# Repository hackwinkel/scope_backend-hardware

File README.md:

# 100Ms/s dual channel 16 bitdigital oscilloscope and function generator back-end with ethernet 

This repository contains the schematics and PCB design files.

# Main features
- 100MHz sample rate
- 2 channels, 16 bits A/D
- 4 channels, 14 bits D/A
- 256 Mbyte ddr3 ram
- Gigabit Ethernet

# General description
Please refer to the hierarchical schematic diagram provided in this repository

* Main (contains various digital power supplies and references to subsheets)
   * FPGA (contains the FPGA with its power connections, JTAG and signal definitions)
   * DACS (contains the D / A convertors with analogue power supplies and output buffers)
   * ADCS (contains the A/D convertors with analogue power supplies and input buffers)
   * ddr3 (contains memory with terminations)
   * GNET (contains Gbit ethernet PHY with magnetics and support components)

## Power supplies
All power supplies are standard LDO regulators, stepping down the voltages from a main 5V connection. To limit dissipation in each LDO, multiple 3.3V, 2.5V, 1.5V and 1.2V subnets are used, and the lower voltages are stepped down via an intermediary 3.3V stage.
The only exception is an optional switched mode power supply module providing +9V/-9V for analogue input/output buffers. This module is optional if the analogue front-end is used, as this also provides these voltages.

## FPGA
This project uses a SPARTAN 6 Field Programmable Logic Array (XC6SLX16 FPLA) at its heart. This FPLA device digitally connects all components, and allows this project to be flexibly reconfigured for various purposes. Core timing is provided by a 100MHz integrated crystal oscillator and a 125MHz clock derived from the ethernet PHY 

## DACS
Digital-to-Analogue conversion is performed by 4 DAC904 165 Msample/s 14 bit D/A convertors. Each of these D/A convertors has its own 3.3V power supply. The DAC904 produces a differential output signal, which is converted and buffered to a single ended signal using an OPA695 operational amplifier.

## ADCS
Analogue-to-Digital conversion is performed by 2 LTC2208 130 Msample/s 16 bit A/D convertors. Each of these A/D convertors has its own 3.3V power supply. For each A/D convertor an AD8138 diferential amplifier provides the required buffered differential analogue drive signal. These AD8138 are by default configured to convert a single ended signal to a differential signal.

## ddr3
A single MT41K128M16 ddr3 RAM chip provides 128M x 16 memory. This has to be a 1.5V compatible device as the SPARTAN 6 FPGA does not support 1.35V memory. Single ended, single direction lines (address and some control signals) are unterminated as this apparently "just works"-albeit probably not at maximum speed. Bidirectional signals are dynamically terminated on the chip. Simple resistive termination is provided on some differential clocking signals. A reference voltage is generated using a resistive divider. All traces on the PCB are length-matched to within 0.5mm

## GNET
A KSZ9031 Gigabit ethernet PHY with Reduced Gigabit Media Independent Interface (RGMII) provides a gigabit ethernet connection through a gigabit MagJack. The local 25Mhz crystal oscillator is converted to a 125MHz clock signal, which is also connected to the FPGA as an alternate timing source

## This project is currently under construction
Most notably, VHDL/Verilog code to program the FPGA is required and an analogue front-end.

# IMPORTANT NOTE FOR PCB FABRICATION

Various PCB houses have various design constraints. JLCPCB has some awkward design rules, requiring a larger space between via-pads and adjacent traces of different nets than between two traces of different nets. KiCAD only allows you to specify *one* spacing for both. In order to accomodate this, the PCB has been designed using 0.508mm vias with 0.2mm holes. Prior to exporting to gerbers, these via pads need to be made smaller in order to compy with these design rules:

Pcbnew -> Setup -> Design rules, change "Via Dia" to 0.45mm
Pcbnew -> Edit -> Edit All Tracks and Vias -> Set all vias (no tracks) to their Netclass value, and OK

## EXPORT GERBERS, DO NOT SAVE THE CHANGED PCB DESIGN FILES as next time you change anything the smaller vias will lead to planes and traces coming too close to the via.

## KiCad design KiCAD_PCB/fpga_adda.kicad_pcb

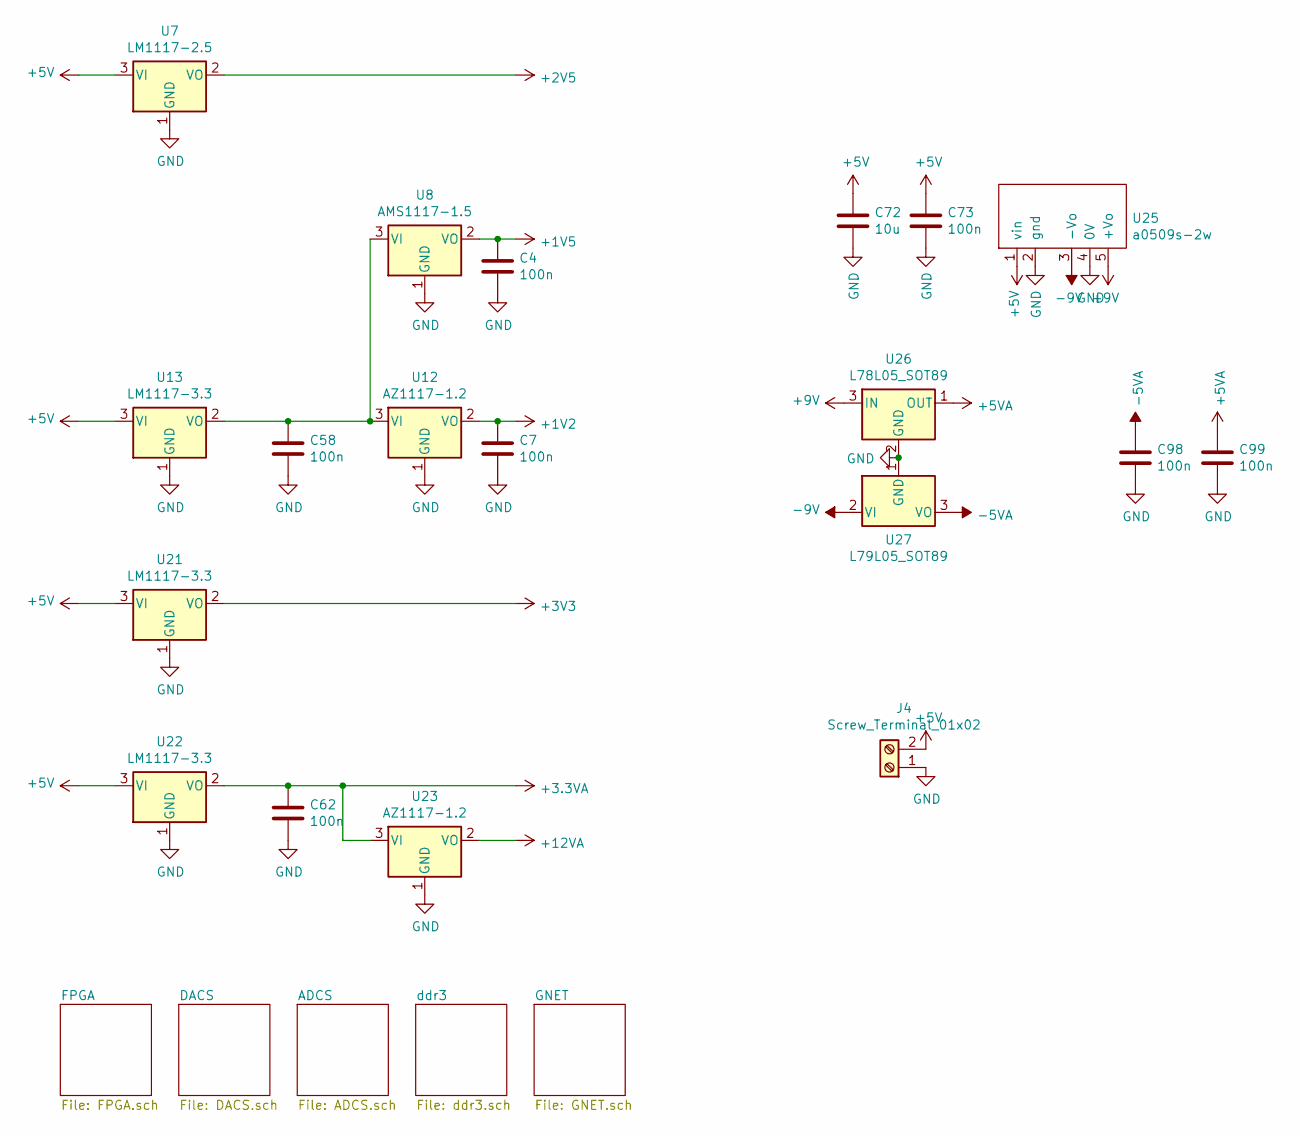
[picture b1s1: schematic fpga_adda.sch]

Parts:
C4, C7, C58, C62, C73, C98, C99: 100n; C_0805_2012Metric_Pad1.15x1.40mm_HandSolder
C72: 10u; C_0805_2012Metric_Pad1.15x1.40mm_HandSolder
J4: Screw_Terminal_01x02; TerminalBlock_bornier-2_P5.08mm
U7: LM1117-2.5; SOT-223-3_TabPin2
U8: AMS1117-1.5; SOT-223-3_TabPin2
U12, U23: AZ1117-1.2; SOT-223-3_TabPin2
U13, U21, U22: LM1117-3.3; SOT-223-3_TabPin2
U25: a0509s-2w
U26: L78L05_SOT89; SOT-89-3
U27: L79L05_SOT89; SOT-89-3

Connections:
+1V2: C7.1, U12.2 (VO); also elsewhere on the board
+1V5: C4.1, U8.2 (VO); also elsewhere on the board
+2V5: U7.2 (VO); also elsewhere on the board
+3.3VA: C62.1, U22.2 (VO), U23.3 (VI); also elsewhere on the board
+5V: C72.1, C73.1, J4.2, U7.3 (VI), U13.3 (VI), U21.3 (VI), U22.3 (VI), U25.1 (vin); also elsewhere on the board
+5VA: C99.1, U26.1 (OUT); also elsewhere on the board
+9V: U25.5 (+Vo), U26.3 (IN)
+12VA: U23.2 (VO); also elsewhere on the board
-5VA: C98.1, U27.3 (VO); also elsewhere on the board
-9V: U25.3 (-Vo), U27.2 (VI)
GND: C4.2, C7.2, C58.2, C62.2, C72.2, C73.2, C98.2, C99.2, J4.1, U7.1 (GND), U8.1 (GND), U12.1 (GND), U13.1 (GND), U21.1 (GND), U22.1 (GND), U23.1 (GND), U25.2 (gnd), U25.4 (0V), U26.2 (GND), U27.1 (GND); also elsewhere on the board
unnamed: C58.1, U8.3 (VI), U12.3 (VI), U13.2 (VO)

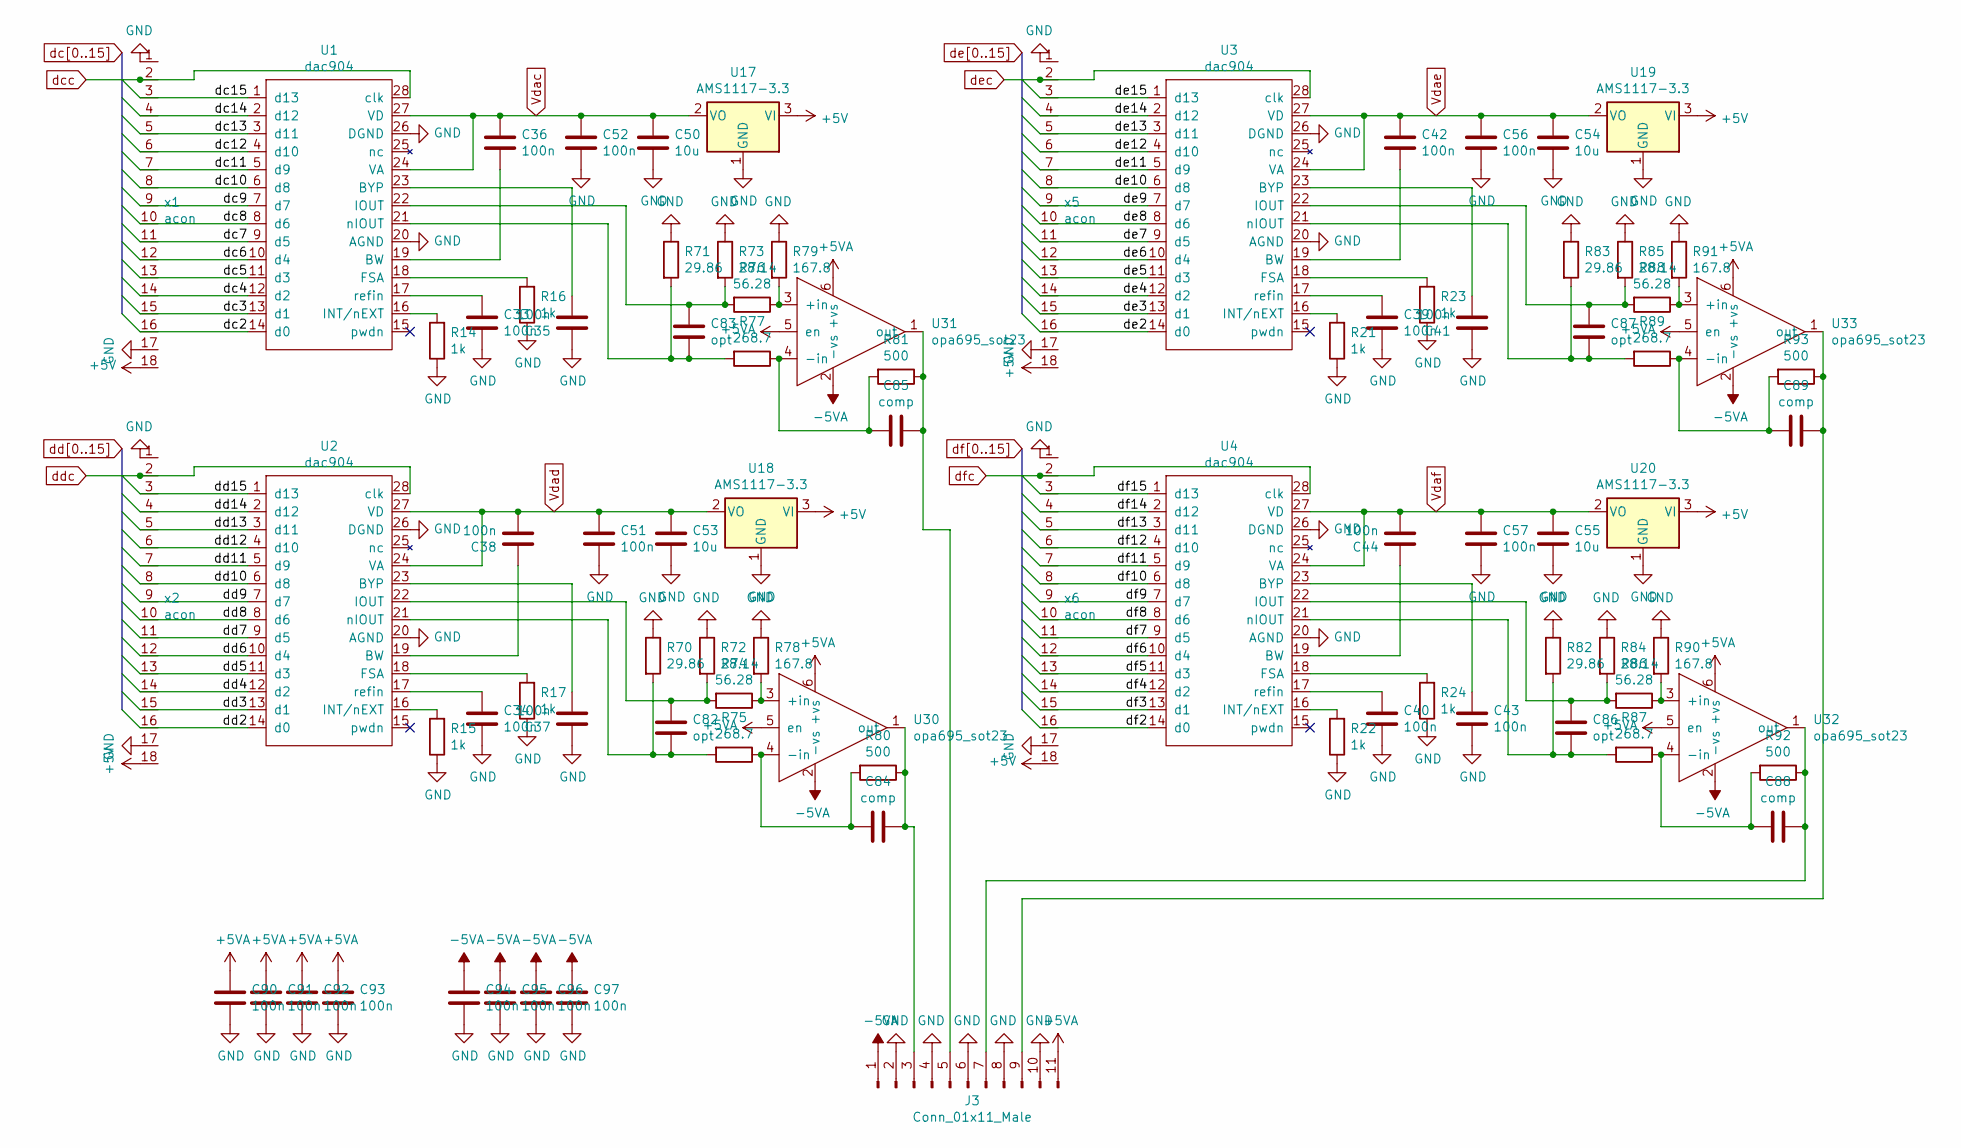
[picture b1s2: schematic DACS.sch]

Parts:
C33, C34, C35, C36, C37, C38, C39, C40, C41, C42, C43, C44, C51, C52, C56, C57, C90, C91, C92, C93, C94, C95, C96, C97: 100n; C_0805_2012Metric_Pad1.15x1.40mm_HandSolder
C50, C53, C54, C55: 10u; C_0805_2012Metric_Pad1.15x1.40mm_HandSolder
C82, C83, C86, C87: opt; C_0805_2012Metric_Pad1.15x1.40mm_HandSolder
C84, C85, C88, C89: comp; C_0805_2012Metric_Pad1.15x1.40mm_HandSolder
J3: Conn_01x11_Male; PinHeader_1x11_P2.54mm_Vertical
R14, R15, R16, R17, R21, R22, R23, R24: 1k; R_0805_2012Metric_Pad1.15x1.40mm_HandSolder
R70, R71, R82, R83: 29.86; R_0805_2012Metric_Pad1.15x1.40mm_HandSolder
R72, R73, R84, R85: 28.14; R_0805_2012Metric_Pad1.15x1.40mm_HandSolder
R74, R76, R86, R88: 56.28; R_0805_2012Metric_Pad1.15x1.40mm_HandSolder
R75, R77, R87, R89: 268.7; R_0805_2012Metric_Pad1.15x1.40mm_HandSolder
R78, R79, R90, R91: 167.8; R_0805_2012Metric_Pad1.15x1.40mm_HandSolder
R80, R81, R92, R93: 500; R_0805_2012Metric_Pad1.15x1.40mm_HandSolder
U1, U2, U3, U4: dac904; SSOP-28_5.3x10.2mm_P0.65mm
U17, U18, U19, U20: AMS1117-3.3; SOT-223-3_TabPin2
U30, U31, U32, U33: opa695_sot23; SOT-23-6_Handsoldering
x1, x2, x5, x6: acon

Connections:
+5V: U17.3 (VI), U18.3 (VI), U19.3 (VI), U20.3 (VI), x1.18, x2.18, x5.18, x6.18; also elsewhere on the board
+5VA: C90.1, C91.1, C92.1, C93.1, J3.11, U30.5 (en), U30.6 (+vs), U31.5 (en), U31.6 (+vs), U32.5 (en), U32.6 (+vs), U33.5 (en), U33.6 (+vs); also elsewhere on the board
-5VA: C94.1, C95.1, C96.1, C97.1, J3.1, U30.2 (-vs), U31.2 (-vs), U32.2 (-vs), U33.2 (-vs); also elsewhere on the board
GND: C33.2, C34.2, C35.1, C37.1, C39.2, C40.2, C41.1, C43.2, C50.2, C51.2, C52.2, C53.2, C54.2, C55.2, C56.2, C57.2, C90.2, C91.2, C92.2, C93.2, C94.2, C95.2, C96.2, C97.2, J3.2, J3.4, J3.6, J3.8, J3.10, R14.1, R15.1, R16.1, R17.1, R21.1, R22.1, R23.1, R24.1, R70.1, R71.1, R72.1, R73.1, R78.1, R79.1, R82.1, R83.1, R84.1, R85.1, R90.1, R91.1, U1.20 (AGND), U1.26 (DGND), U2.20 (AGND), U2.26 (DGND), U3.20 (AGND), U3.26 (DGND), U4.20 (AGND), U4.26 (DGND), U17.1 (GND), U18.1 (GND), U19.1 (GND), U20.1 (GND), x1.1, x1.17, x2.1, x2.17, x5.1, x5.17, x6.1, x6.17; also elsewhere on the board
unnamed: C33.1, U1.17 (refin)
unnamed: C34.1, U2.17 (refin)
unnamed: C35.2, U1.23 (BYP)
unnamed: C36.2, U1.19 (BW)
unnamed: C37.2, U2.23 (BYP)
unnamed: C38.1, U2.19 (BW)
unnamed: C39.1, U3.17 (refin)
unnamed: C40.1, U4.17 (refin)
unnamed: C41.2, U3.23 (BYP)
unnamed: C42.2, U3.19 (BW)
unnamed: C43.1, U4.23 (BYP)
unnamed: C44.1, U4.19 (BW)
unnamed: C82.1, R72.2, R74.2, U2.22 (IOUT)
unnamed: C82.2, R70.2, R75.2, U2.21 (nIOUT)
unnamed: C83.1, R73.2, R76.2, U1.22 (IOUT)
unnamed: C83.2, R71.2, R77.2, U1.21 (nIOUT)
unnamed: C84.1, J3.3, R80.1, U30.1 (out)
unnamed: C84.2, R75.1, R80.2, U30.4 (-in)
unnamed: C85.1, J3.5, R81.1, U31.1 (out)
unnamed: C85.2, R77.1, R81.2, U31.4 (-in)
unnamed: C86.1, R84.2, R86.2, U4.22 (IOUT)
unnamed: C86.2, R82.2, R87.2, U4.21 (nIOUT)
unnamed: C87.1, R85.2, R88.2, U3.22 (IOUT)
unnamed: C87.2, R83.2, R89.2, U3.21 (nIOUT)
unnamed: C88.1, J3.7, R92.1, U32.1 (out)
unnamed: C88.2, R87.1, R92.2, U32.4 (-in)
unnamed: C89.1, J3.9, R93.1, U33.1 (out)
unnamed: C89.2, R89.1, R93.2, U33.4 (-in)
unnamed: R14.2, U1.16 (INT/nEXT)
unnamed: R15.2, U2.16 (INT/nEXT)
unnamed: R16.2, U1.18 (FSA)
unnamed: R17.2, U2.18 (FSA)
unnamed: R21.2, U3.16 (INT/nEXT)
unnamed: R22.2, U4.16 (INT/nEXT)
unnamed: R23.2, U3.18 (FSA)
unnamed: R24.2, U4.18 (FSA)
unnamed: R74.1, R78.2, U30.3 (+in)
unnamed: R76.1, R79.2, U31.3 (+in)
unnamed: R86.1, R90.2, U32.3 (+in)
unnamed: R88.1, R91.2, U33.3 (+in)
Vdac: C36.1, C50.1, C52.1, U1.24 (VA), U1.27 (VD), U17.2 (VO)
Vdad: C38.2, C51.1, C53.1, U2.24 (VA), U2.27 (VD), U18.2 (VO)
Vdae: C42.1, C54.1, C56.1, U3.24 (VA), U3.27 (VD), U19.2 (VO)
Vdaf: C44.2, C55.1, C57.1, U4.24 (VA), U4.27 (VD), U20.2 (VO)
dc2: U1.14 (d0), x1.16; also elsewhere on the board
dc3: U1.13 (d1), x1.15; also elsewhere on the board
dc4: U1.12 (d2), x1.14; also elsewhere on the board
dc5: U1.11 (d3), x1.13; also elsewhere on the board
dc6: U1.10 (d4), x1.12; also elsewhere on the board
dc7: U1.9 (d5), x1.11; also elsewhere on the board
dc8: U1.8 (d6), x1.10; also elsewhere on the board
dc9: U1.7 (d7), x1.9; also elsewhere on the board
dc10: U1.6 (d8), x1.8; also elsewhere on the board
dc11: U1.5 (d9), x1.7; also elsewhere on the board
dc12: U1.4 (d10), x1.6; also elsewhere on the board
dc13: U1.3 (d11), x1.5; also elsewhere on the board
dc14: U1.2 (d12), x1.4; also elsewhere on the board
dc15: U1.1 (d13), x1.3; also elsewhere on the board
dcc: U1.28 (clk), x1.2; also elsewhere on the board
dd2: U2.14 (d0), x2.16; also elsewhere on the board
dd3: U2.13 (d1), x2.15; also elsewhere on the board
dd4: U2.12 (d2), x2.14; also elsewhere on the board
dd5: U2.11 (d3), x2.13; also elsewhere on the board
dd6: U2.10 (d4), x2.12; also elsewhere on the board
dd7: U2.9 (d5), x2.11; also elsewhere on the board
dd8: U2.8 (d6), x2.10; also elsewhere on the board
dd9: U2.7 (d7), x2.9; also elsewhere on the board
dd10: U2.6 (d8), x2.8; also elsewhere on the board
dd11: U2.5 (d9), x2.7; also elsewhere on the board
dd12: U2.4 (d10), x2.6; also elsewhere on the board
dd13: U2.3 (d11), x2.5; also elsewhere on the board
dd14: U2.2 (d12), x2.4; also elsewhere on the board
dd15: U2.1 (d13), x2.3; also elsewhere on the board
ddc: U2.28 (clk), x2.2; also elsewhere on the board
de2: U3.14 (d0), x5.16; also elsewhere on the board
de3: U3.13 (d1), x5.15; also elsewhere on the board
de4: U3.12 (d2), x5.14; also elsewhere on the board
de5: U3.11 (d3), x5.13; also elsewhere on the board
de6: U3.10 (d4), x5.12; also elsewhere on the board
de7: U3.9 (d5), x5.11; also elsewhere on the board
de8: U3.8 (d6), x5.10; also elsewhere on the board
de9: U3.7 (d7), x5.9; also elsewhere on the board
de10: U3.6 (d8), x5.8; also elsewhere on the board
de11: U3.5 (d9), x5.7; also elsewhere on the board
de12: U3.4 (d10), x5.6; also elsewhere on the board
de13: U3.3 (d11), x5.5; also elsewhere on the board
de14: U3.2 (d12), x5.4; also elsewhere on the board
de15: U3.1 (d13), x5.3; also elsewhere on the board
dec: U3.28 (clk), x5.2; also elsewhere on the board
df2: U4.14 (d0), x6.16; also elsewhere on the board
df3: U4.13 (d1), x6.15; also elsewhere on the board
df4: U4.12 (d2), x6.14; also elsewhere on the board
df5: U4.11 (d3), x6.13; also elsewhere on the board
df6: U4.10 (d4), x6.12; also elsewhere on the board
df7: U4.9 (d5), x6.11; also elsewhere on the board
df8: U4.8 (d6), x6.10; also elsewhere on the board
df9: U4.7 (d7), x6.9; also elsewhere on the board
df10: U4.6 (d8), x6.8; also elsewhere on the board
df11: U4.5 (d9), x6.7; also elsewhere on the board
df12: U4.4 (d10), x6.6; also elsewhere on the board
df13: U4.3 (d11), x6.5; also elsewhere on the board
df14: U4.2 (d12), x6.4; also elsewhere on the board
df15: U4.1 (d13), x6.3; also elsewhere on the board
dfc: U4.28 (clk), x6.2; also elsewhere on the board

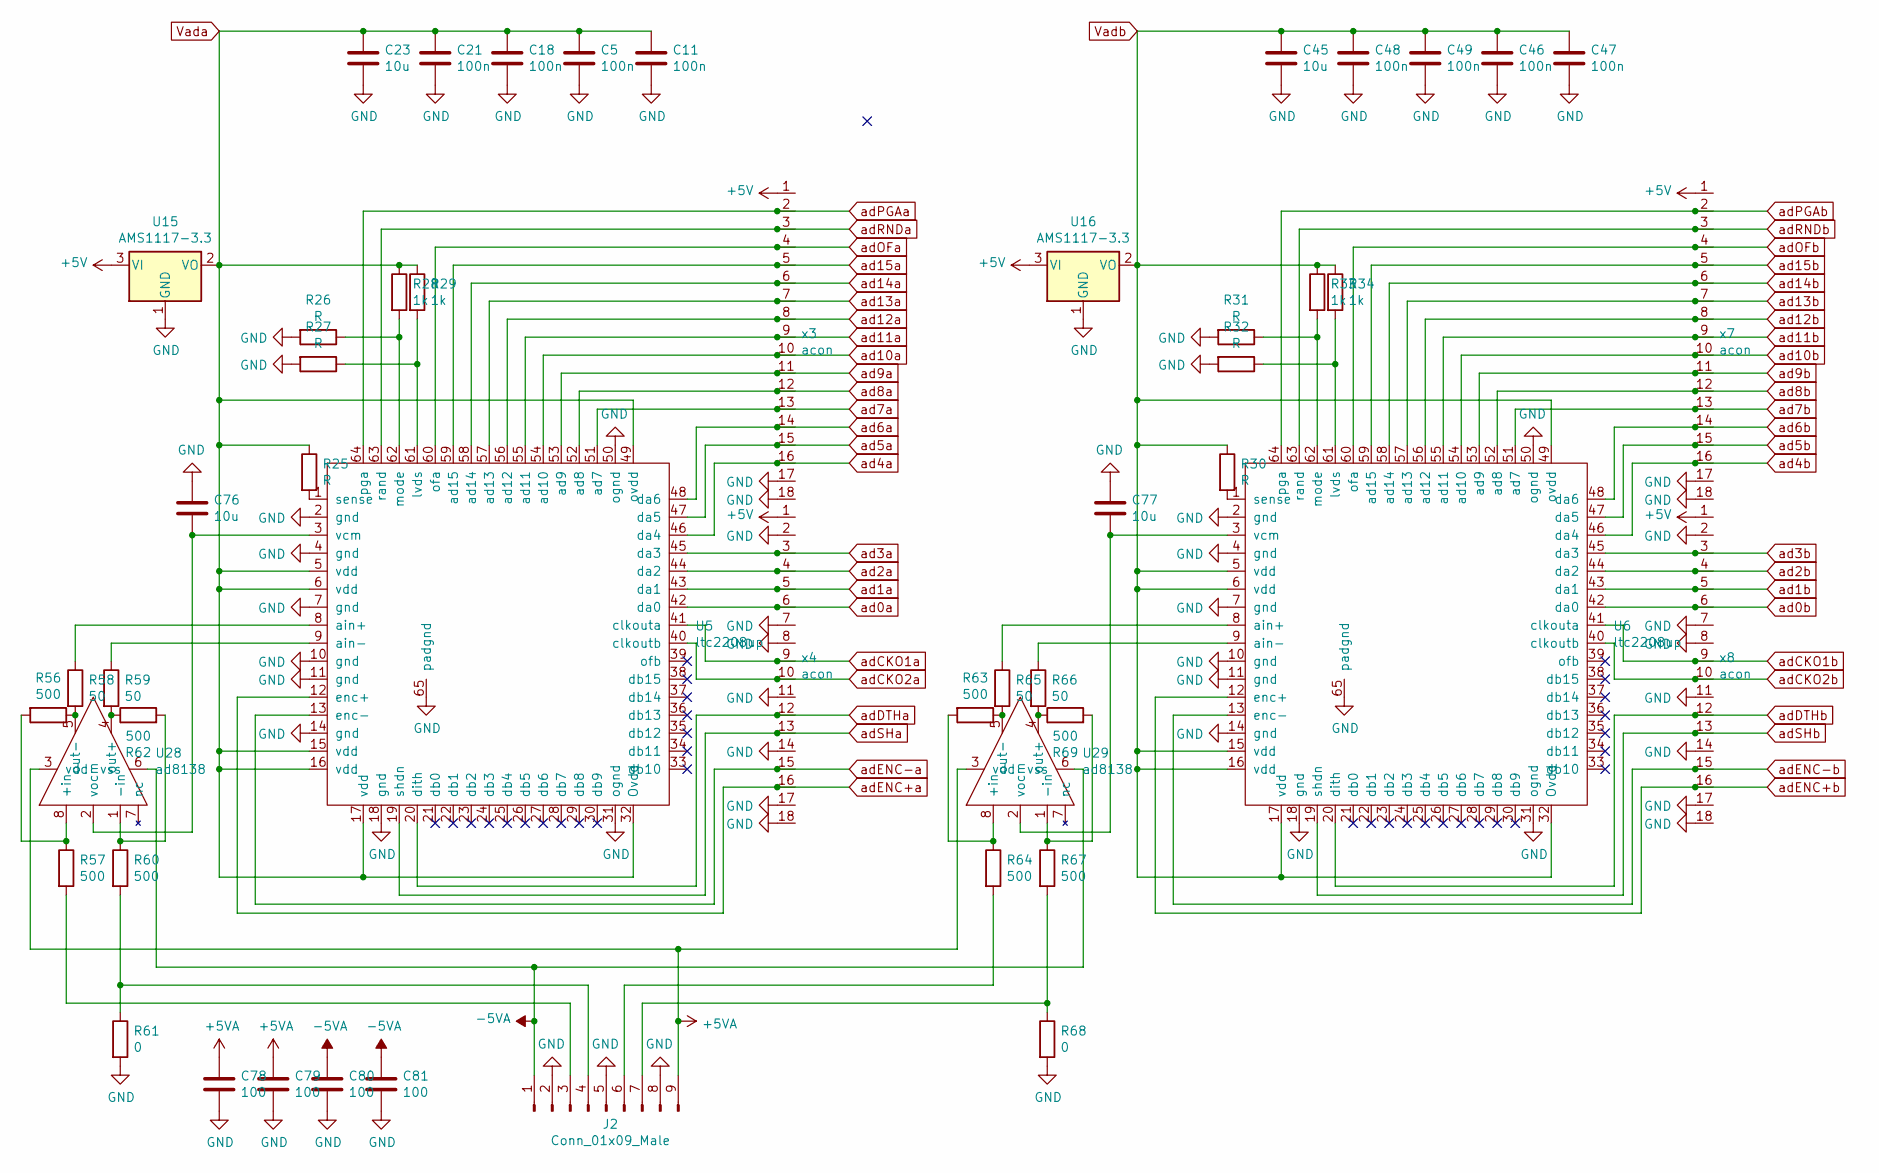
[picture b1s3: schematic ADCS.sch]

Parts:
C5, C11, C18, C21, C46, C47, C48, C49: 100n; C_0805_2012Metric_Pad1.15x1.40mm_HandSolder
C23, C45, C76, C77: 10u; C_0805_2012Metric_Pad1.15x1.40mm_HandSolder
C78, C79, C80, C81: 100; C_0805_2012Metric_Pad1.15x1.40mm_HandSolder
J2: Conn_01x09_Male; PinHeader_1x09_P2.54mm_Vertical
R25, R26, R27, R30, R31, R32: R; R_0805_2012Metric_Pad1.15x1.40mm_HandSolder
R28, R29, R33, R34: 1k; R_0805_2012Metric_Pad1.15x1.40mm_HandSolder
R56, R57, R60, R62, R63, R64, R67, R69: 500; R_0805_2012Metric_Pad1.15x1.40mm_HandSolder
R58, R59, R65, R66: 50; R_0805_2012Metric_Pad1.15x1.40mm_HandSolder
R61, R68: 0; R_0805_2012Metric_Pad1.15x1.40mm_HandSolder
U5, U6: ltc2208up; ltc2208
U15, U16: AMS1117-3.3; SOT-223-3_TabPin2
U28, U29: ad8138; SO-8_5.3x6.2mm_P1.27mm
x3, x4, x7, x8: acon

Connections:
+5V: U15.3 (VI), U16.3 (VI), x3.1, x4.1, x7.1, x8.1; also elsewhere on the board
+5VA: C78.1, C79.1, J2.9, U28.3 (vdd), U29.3 (vdd); also elsewhere on the board
-5VA: C80.1, C81.1, J2.1, U28.6 (vss), U29.6 (vss); also elsewhere on the board
GND: C5.2, C11.2, C18.2, C21.2, C23.2, C45.2, C46.2, C47.2, C48.2, C49.2, C76.2, C77.1, C78.2, C79.2, C80.2, C81.2, J2.2, J2.5, J2.8, R26.2, R27.2, R31.2, R32.2, R61.2, R68.2, U5.2 (gnd), U5.4 (gnd), U5.7 (gnd), U5.10 (gnd), U5.11 (gnd), U5.14 (gnd), U5.18 (gnd), U5.31 (ognd), U5.50 (ognd), U5.65 (padgnd), U6.2 (gnd), U6.4 (gnd), U6.7 (gnd), U6.10 (gnd), U6.11 (gnd), U6.14 (gnd), U6.18 (gnd), U6.31 (ognd), U6.50 (ognd), U6.65 (padgnd), U15.1 (GND), U16.1 (GND), x3.17, x3.18, x4.2, x4.7, x4.8, x4.11, x4.14, x4.17, x4.18, x7.17, x7.18, x8.2, x8.7, x8.8, x8.11, x8.14, x8.17, x8.18; also elsewhere on the board
unnamed: C76.1, U5.3 (vcm), U28.2 (vocm)
unnamed: C77.2, U6.3 (vcm), U29.2 (vocm)
unnamed: J2.3, R57.2
unnamed: J2.4, R60.2, R61.1
unnamed: J2.6, R64.2
unnamed: J2.7, R67.2, R68.1
unnamed: R25.2, U5.1 (sense)
unnamed: R26.1, R28.2, U5.62 (mode)
unnamed: R27.1, R29.2, U5.61 (lvds)
unnamed: R30.2, U6.1 (sense)
unnamed: R31.1, R33.2, U6.62 (mode)
unnamed: R32.1, R34.2, U6.61 (lvds)
unnamed: R56.1, R58.2, U28.5 (out-)
unnamed: R56.2, R57.1, U28.8 (+in)
unnamed: R58.1, U5.8 (ain+)
unnamed: R59.1, U5.9 (ain-)
unnamed: R59.2, R62.1, U28.4 (out+)
unnamed: R60.1, R62.2, U28.1 (-in)
unnamed: R63.1, R65.2, U29.5 (out-)
unnamed: R63.2, R64.1, U29.8 (+in)
unnamed: R65.1, U6.8 (ain+)
unnamed: R66.1, U6.9 (ain-)
unnamed: R66.2, R69.1, U29.4 (out+)
unnamed: R67.1, R69.2, U29.1 (-in)
Vada: C5.1, C11.1, C18.1, C21.1, C23.1, R25.1, R28.1, R29.1, U5.5 (vdd), U5.6 (vdd), U5.15 (vdd), U5.16 (vdd), U5.17 (vdd), U5.32 (Ovdd), U5.49 (ovdd), U15.2 (VO)
Vadb: C45.1, C46.1, C47.1, C48.1, C49.1, R30.1, R33.1, R34.1, U6.5 (vdd), U6.6 (vdd), U6.15 (vdd), U6.16 (vdd), U6.17 (vdd), U6.32 (Ovdd), U6.49 (ovdd), U16.2 (VO)
ad0a: U5.42 (da0), x4.6; also elsewhere on the board
ad0b: U6.42 (da0), x8.6; also elsewhere on the board
ad1a: U5.43 (da1), x4.5; also elsewhere on the board
ad1b: U6.43 (da1), x8.5; also elsewhere on the board
ad2a: U5.44 (da2), x4.4; also elsewhere on the board
ad2b: U6.44 (da2), x8.4; also elsewhere on the board
ad3a: U5.45 (da3), x4.3; also elsewhere on the board
ad3b: U6.45 (da3), x8.3; also elsewhere on the board
ad4a: U5.46 (da4), x3.16; also elsewhere on the board
ad4b: U6.46 (da4), x7.16; also elsewhere on the board
ad5a: U5.47 (da5), x3.15; also elsewhere on the board
ad5b: U6.47 (da5), x7.15; also elsewhere on the board
ad6a: U5.48 (da6), x3.14; also elsewhere on the board
ad6b: U6.48 (da6), x7.14; also elsewhere on the board
ad7a: U5.51 (ad7), x3.13; also elsewhere on the board
ad7b: U6.51 (ad7), x7.13; also elsewhere on the board
ad8a: U5.52 (ad8), x3.12; also elsewhere on the board
ad8b: U6.52 (ad8), x7.12; also elsewhere on the board
ad9a: U5.53 (ad9), x3.11; also elsewhere on the board
ad9b: U6.53 (ad9), x7.11; also elsewhere on the board
ad10a: U5.54 (ad10), x3.10; also elsewhere on the board
ad10b: U6.54 (ad10), x7.10; also elsewhere on the board
ad11a: U5.55 (ad11), x3.9; also elsewhere on the board
ad11b: U6.55 (ad11), x7.9; also elsewhere on the board
ad12a: U5.56 (ad12), x3.8; also elsewhere on the board
ad12b: U6.56 (ad12), x7.8; also elsewhere on the board
ad13a: U5.57 (ad13), x3.7; also elsewhere on the board
ad13b: U6.57 (ad13), x7.7; also elsewhere on the board
ad14a: U5.58 (ad14), x3.6; also elsewhere on the board
ad14b: U6.58 (ad14), x7.6; also elsewhere on the board
ad15a: U5.59 (ad15), x3.5; also elsewhere on the board
ad15b: U6.59 (ad15), x7.5; also elsewhere on the board
adCKO1a: U5.41 (clkouta), x4.9; also elsewhere on the board
adCKO1b: U6.41 (clkouta), x8.9; also elsewhere on the board
adCKO2a: U5.40 (clkoutb), x4.10; also elsewhere on the board
adCKO2b: U6.40 (clkoutb), x8.10; also elsewhere on the board
adDTHa: U5.20 (dith), x4.12; also elsewhere on the board
adDTHb: U6.20 (dith), x8.12; also elsewhere on the board
adENC+a: U5.12 (enc+), x4.16; also elsewhere on the board
adENC+b: U6.12 (enc+), x8.16; also elsewhere on the board
adENC-a: U5.13 (enc-), x4.15; also elsewhere on the board
adENC-b: U6.13 (enc-), x8.15; also elsewhere on the board
adOFa: U5.60 (ofa), x3.4; also elsewhere on the board
adOFb: U6.60 (ofa), x7.4; also elsewhere on the board
adPGAa: U5.64 (pga), x3.2; also elsewhere on the board
adPGAb: U6.64 (pga), x7.2; also elsewhere on the board
adRNDa: U5.63 (rand), x3.3; also elsewhere on the board
adRNDb: U6.63 (rand), x7.3; also elsewhere on the board
adSHa: U5.19 (shdn), x4.13; also elsewhere on the board
adSHb: U6.19 (shdn), x8.13; also elsewhere on the board

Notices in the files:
KiCAD_PCB/fpga_adda.kicad_pcb:
(c)2020 T.J.A.Borm
(c)2020
(c)2020 T.Borm
